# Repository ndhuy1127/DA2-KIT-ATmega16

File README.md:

# KIT phát triển ATmega16

Đồ án 2 – Học kỳ 20261 – Đại học Bách khoa Hà Nội

- **Mã lớp / mã đề tài:** 772645 / DA26111
- **Sinh viên thực hiện:** Nguyễn Đức Huy – 20233448
- **Giảng viên hướng dẫn:** ThS. Nguyễn Minh Đức

Đề tài thiết kế và lập trình một bo KIT dùng ATmega16. Trên bo có khối nguồn 5 V, thạch anh 8 MHz,
cổng nạp ISP cho USBasp, 8 LED đơn, 2 nút nhấn nối vào ngắt ngoài, biến trở để thử ADC, cổng UART,
chỗ cắm LCD1602 và bàn phím 4×4, cùng 4 header để đưa các cổng PORTA–PORTD ra ngoài.

## Tiến độ

| Tuần | Nội dung | Tài liệu | Trạng thái |
|------|----------|----------|------------|
| 1 | Tìm hiểu yêu cầu, datasheet, sơ đồ khối | [tuan-01](docs/tuan-01/yeu-cau-va-so-do-khoi.md) | Xong |
| 2 | Phân chân, chọn linh kiện, BOM | [pinmap](docs/tuan-02/pinmap.md), [BOM](docs/tuan-02/bom.md) | Xong |
| 3 | Vẽ schematic, ERC | [tuan-03](docs/tuan-03/schematic.md), [PDF](hardware/output/KIT-ATmega16-schematic.pdf) | Xong |
| 4 | Vẽ PCB, DRC, xuất Gerber | [tuan-04](docs/tuan-04/pcb.md), [Gerber](hardware/output/KIT-ATmega16-gerber.zip) | Xong |
| 5 | Mô phỏng GPIO, nút nhấn, ngắt ngoài, Timer | [tuan-05](docs/tuan-05/mo-phong.md), [firmware](firmware/labs) | Đang làm |
| 6 | Mô phỏng ADC, UART | | |
| 7 | Mô phỏng LCD1602, bàn phím 4×4 | | |
| 8 | Bài tổng hợp, hàn lắp bo | | |
| 9 | Chạy trên bo thật, đo kiểm | | |
| 10 | Báo cáo, slide, demo | | |

Lịch chi tiết xem ở [docs/ke-hoach/ke-hoach-dieu-chinh.md](docs/ke-hoach/ke-hoach-dieu-chinh.md).

## Thư mục

```
docs/          kế hoạch, phiếu báo cáo tuần, tài liệu từng tuần
hardware/      project KiCad, file xuất (PDF, Gerber, BOM, ảnh 3D) và script hỗ trợ
firmware/      mã nguồn các bài lab, board.h chứa phân chân dùng chung
simulation/    mạch mô phỏng Proteus
```

## Build firmware

Trên Windows cài avr-gcc bằng Scoop (`scoop install avr-gcc`), sau đó:

```powershell
cd firmware
powershell -ExecutionPolicy Bypass -File build.ps1                       # build hết, ra build/*.hex
powershell -ExecutionPolicy Bypass -File build.ps1 -Lab 04_timer -Flash  # build và nạp 1 bài qua USBasp
```

Với chip mới cần ghi fuse một lần để chạy thạch anh 8 MHz và tắt JTAG:

```bash
avrdude -c usbasp -p m16 -U lfuse:w:0xFF:m -U hfuse:w:0xD9:m
```

## Phần cứng

Mở `hardware/kicad/KIT-ATmega16.kicad_pro` bằng KiCad 10. Schematic chạy ERC không còn lỗi;
PCB chạy DRC không còn lỗi và khớp với schematic, chỉ còn vài cảnh báo chữ silkscreen bị chồng.

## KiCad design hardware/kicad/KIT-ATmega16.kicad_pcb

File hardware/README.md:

# Phần cứng

- `kicad/` – project KiCad 10 (`KIT-ATmega16.kicad_pro`), báo cáo ERC, DRC và netlist.
- `output/` – schematic PDF, file Gerber nén, BOM, ảnh 3D và bản in từng lớp.
- `scripts/` – các script Python hỗ trợ:
  - `design.py`: danh sách linh kiện, footprint và cách nối dây.
  - `gen_schematic.py`: tạo file schematic từ `design.py`.
  - `check_netlist.py`: so netlist KiCad với `design.py` để bắt chỗ nối sai.
  - `gen_pcb.py`: đặt linh kiện lên PCB, trao đổi với Freerouting để đi dây, đổ đồng GND.

## Chạy lại các bước

Cần KiCad 10 và Python 3. Riêng bước đi dây cần thêm Java 25 và `freerouting-2.5.0.jar`.

```bash
export KICAD_BIN="/c/Users/<user>/AppData/Local/Programs/KiCad/10.0/bin"
sh hardware/build_sch.sh      # tạo schematic, chạy ERC, xuất netlist, kiểm tra, xuất PDF

export JAVA="<java 25>/bin/java.exe"
export FREEROUTING="<đường dẫn>/freerouting-2.5.0.jar"
sh hardware/build_pcb.sh      # đặt linh kiện, đi dây, đổ đồng, chạy DRC, xuất Gerber, BOM, ảnh 3D
```

Lưu ý: `build_pcb.sh` đặt và đi dây lại từ đầu, nên sẽ ghi đè những gì đã chỉnh tay trên PCB. Khi đã sửa
layout trong KiCad thì chỉ chạy riêng các lệnh `kicad-cli pcb drc` và `export`.

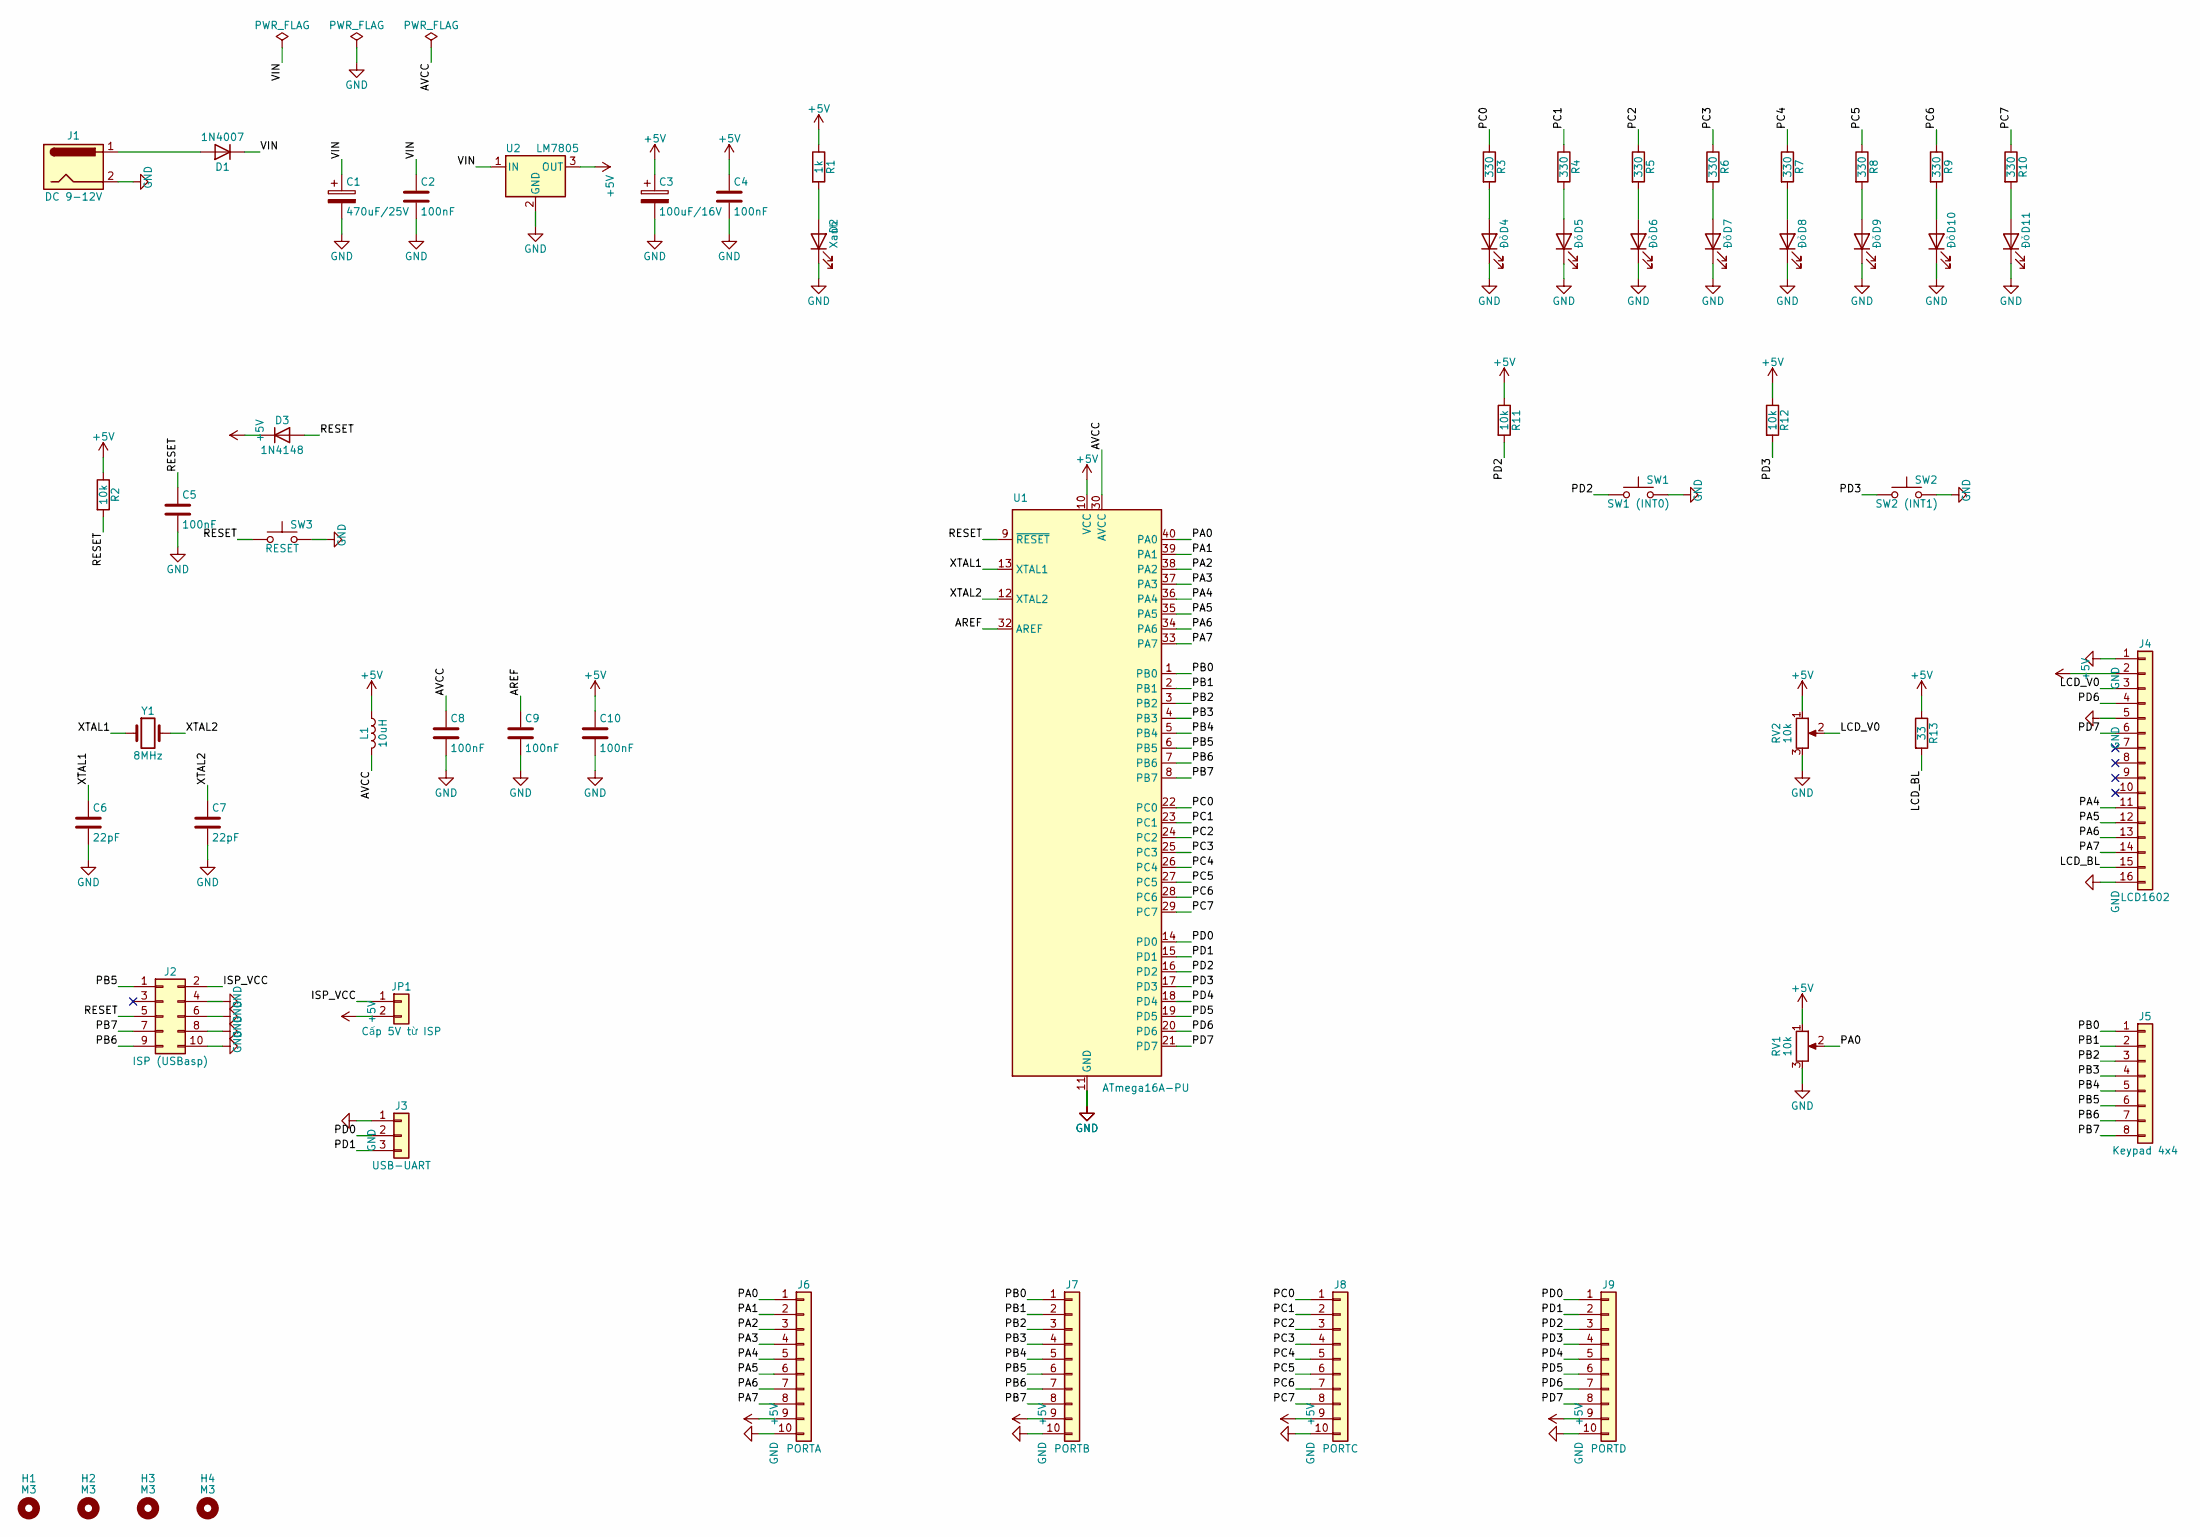
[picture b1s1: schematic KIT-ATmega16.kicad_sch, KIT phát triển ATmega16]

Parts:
C1: 470uF/25V; CP_Radial_D10.0mm_P5.00mm
C2, C4, C5, C8, C9, C10: 100nF; C_Disc_D5.0mm_W2.5mm_P5.00mm
C3: 100uF/16V; CP_Radial_D6.3mm_P2.50mm
C6, C7: 22pF; C_Disc_D5.0mm_W2.5mm_P5.00mm
D1: 1N4007; D_DO-41_SOD81_P10.16mm_Horizontal
D2: Xanh; LED_D3.0mm
D3: 1N4148; D_DO-35_SOD27_P7.62mm_Horizontal
D4, D5, D6, D7, D8, D9, D10, D11: Đỏ; LED_D3.0mm
H1, H2, H3, H4: M3; MountingHole_3.2mm_M3
J1: DC 9-12V; BarrelJack_Horizontal
J2: ISP (USBasp); IDC-Header_2x05_P2.54mm_Vertical
J3: USB-UART; PinHeader_1x03_P2.54mm_Vertical
J4: LCD1602; PinSocket_1x16_P2.54mm_Vertical
J5: Keypad 4x4; PinSocket_1x08_P2.54mm_Vertical
J6: PORTA; PinHeader_1x10_P2.54mm_Vertical
J7: PORTB; PinHeader_1x10_P2.54mm_Vertical
J8: PORTC; PinHeader_1x10_P2.54mm_Vertical
J9: PORTD; PinHeader_1x10_P2.54mm_Vertical
JP1: Cấp 5V từ ISP; PinHeader_1x02_P2.54mm_Vertical
L1: 10uH; L_Axial_L5.3mm_D2.2mm_P10.16mm_Horizontal_Vishay_IM-1
R1: 1k; R_Axial_DIN0207_L6.3mm_D2.5mm_P10.16mm_Horizontal
R2, R11, R12: 10k; R_Axial_DIN0207_L6.3mm_D2.5mm_P10.16mm_Horizontal
R3, R4, R5, R6, R7, R8, R9, R10: 330; R_Axial_DIN0207_L6.3mm_D2.5mm_P10.16mm_Horizontal
R13: 33; R_Axial_DIN0207_L6.3mm_D2.5mm_P10.16mm_Horizontal
RV1, RV2: 10k; Potentiometer_Bourns_3386P_Vertical
SW1: SW1 (INT0); SW_PUSH_6mm
SW2: SW2 (INT1); SW_PUSH_6mm
SW3: RESET; SW_PUSH_6mm
U1: ATmega16A-PU; DIP-40_W15.24mm_Socket
U2: LM7805; TO-220-3_Vertical
Y1: 8MHz; Crystal_HC49-U_Vertical

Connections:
+5V: C3.1, C4.1, C10.1, D3.1 (K), J4.2, J6.9, J7.9, J8.9, J9.9, JP1.2, L1.1, R1.1, R2.1, R11.1, R12.1, R13.1, RV1.1, RV2.1, U1.10 (VCC), U2.3 (OUT)
/AREF: C9.1, U1.32 (AREF)
/AVCC: C8.1, L1.2, U1.30 (AVCC)
/ISP_VCC: J2.2, JP1.1
/LCD_BL: J4.15, R13.2
/LCD_V0: J4.3, RV2.2
/PA0: J6.1, RV1.2, U1.40 (PA0)
/PA1: J6.2, U1.39 (PA1)
/PA2: J6.3, U1.38 (PA2)
/PA3: J6.4, U1.37 (PA3)
/PA4: J4.11, J6.5, U1.36 (PA4)
/PA5: J4.12, J6.6, U1.35 (PA5)
/PA6: J4.13, J6.7, U1.34 (PA6)
/PA7: J4.14, J6.8, U1.33 (PA7)
/PB0: J5.1, J7.1, U1.1 (PB0)
/PB1: J5.2, J7.2, U1.2 (PB1)
/PB2: J5.3, J7.3, U1.3 (PB2)
/PB3: J5.4, J7.4, U1.4 (PB3)
/PB4: J5.5, J7.5, U1.5 (PB4)
/PB5: J2.1, J5.6, J7.6, U1.6 (PB5)
/PB6: J2.9, J5.7, J7.7, U1.7 (PB6)
/PB7: J2.7, J5.8, J7.8, U1.8 (PB7)
/PC0: J8.1, R3.1, U1.22 (PC0)
/PC1: J8.2, R4.1, U1.23 (PC1)
/PC2: J8.3, R5.1, U1.24 (PC2)
/PC3: J8.4, R6.1, U1.25 (PC3)
/PC4: J8.5, R7.1, U1.26 (PC4)
/PC5: J8.6, R8.1, U1.27 (PC5)
/PC6: J8.7, R9.1, U1.28 (PC6)
/PC7: J8.8, R10.1, U1.29 (PC7)
/PD0: J3.2, J9.1, U1.14 (PD0)
/PD1: J3.3, J9.2, U1.15 (PD1)
/PD2: J9.3, R11.2, SW1.1, U1.16 (PD2)
/PD3: J9.4, R12.2, SW2.1, U1.17 (PD3)
/PD4: J9.5, U1.18 (PD4)
/PD5: J9.6, U1.19 (PD5)
/PD6: J4.4, J9.7, U1.20 (PD6)
/PD7: J4.6, J9.8, U1.21 (PD7)
/RESET: C5.1, D3.2 (A), J2.5, R2.2, SW3.1, U1.9 (~RESET)
/VIN: C1.1, C2.1, D1.1 (K), U2.1 (IN)
/XTAL1: C6.1, U1.13 (XTAL1), Y1.1
/XTAL2: C7.1, U1.12 (XTAL2), Y1.2
GND: C1.2, C2.2, C3.2, C4.2, C5.2, C6.2, C7.2, C8.2, C9.2, C10.2, D2.1 (K), D4.1 (K), D5.1 (K), D6.1 (K), D7.1 (K), D8.1 (K), D9.1 (K), D10.1 (K), D11.1 (K), J1.2, J2.4, J2.6, J2.8, J2.10, J3.1, J4.1, J4.5, J4.16, J6.10, J7.10, J8.10, J9.10, RV1.3, RV2.3, SW1.2, SW2.2, SW3.2, U1.11 (GND), U1.31 (GND), U2.2 (GND)
unnamed: D1.2 (A), J1.1
unnamed: D2.2 (A), R1.2
unnamed: D4.2 (A), R3.2
unnamed: D5.2 (A), R4.2
unnamed: D6.2 (A), R5.2
unnamed: D7.2 (A), R6.2
unnamed: D8.2 (A), R7.2
unnamed: D9.2 (A), R8.2
unnamed: D10.2 (A), R9.2
unnamed: D11.2 (A), R10.2

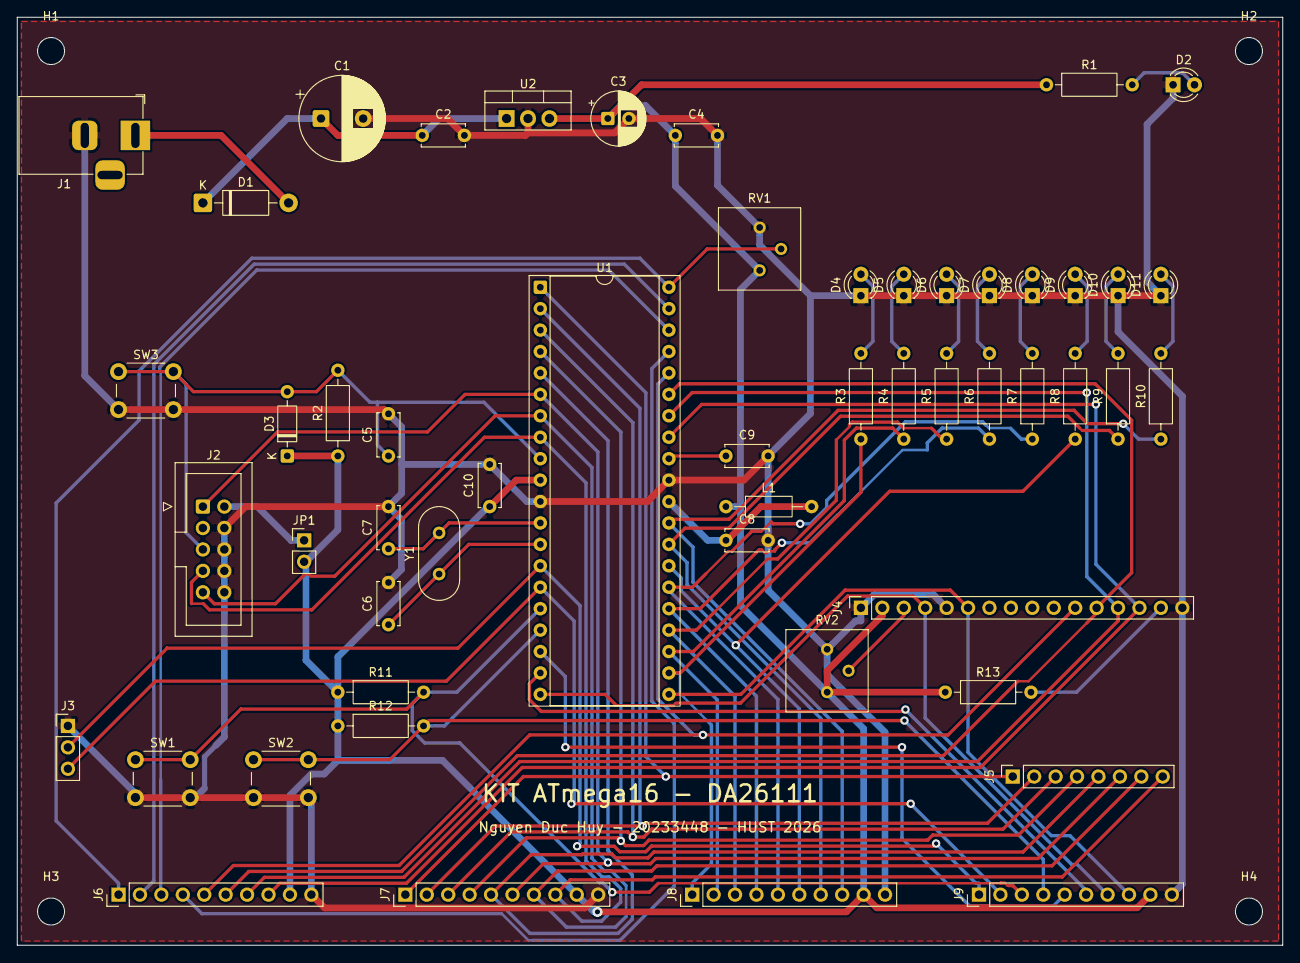
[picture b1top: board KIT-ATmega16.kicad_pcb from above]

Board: 2 copper layers, 150.0 x 110.0 mm, 57 parts (0 on the bottom side), 53 nets.

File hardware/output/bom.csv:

"Reference","Value","Footprint","QUANTITY"
"C1","470uF/25V","Capacitor_THT:CP_Radial_D10.0mm_P5.00mm","1"
"C2,C4,C5,C8-C10","100nF","Capacitor_THT:C_Disc_D5.0mm_W2.5mm_P5.00mm","6"
"C3","100uF/16V","Capacitor_THT:CP_Radial_D6.3mm_P2.50mm","1"
"C6,C7","22pF","Capacitor_THT:C_Disc_D5.0mm_W2.5mm_P5.00mm","2"
"D1","1N4007","Diode_THT:D_DO-41_SOD81_P10.16mm_Horizontal","1"
"D2","Xanh","LED_THT:LED_D3.0mm","1"
"D3","1N4148","Diode_THT:D_DO-35_SOD27_P7.62mm_Horizontal","1"
"D4-D11","Đỏ","LED_THT:LED_D3.0mm","8"
"J1","DC 9-12V","Connector_BarrelJack:BarrelJack_Horizontal","1"
"J2","ISP (USBasp)","Connector_IDC:IDC-Header_2x05_P2.54mm_Vertical","1"
"J3","USB-UART","Connector_PinHeader_2.54mm:PinHeader_1x03_P2.54mm_Vertical","1"
"J4","LCD1602","Connector_PinSocket_2.54mm:PinSocket_1x16_P2.54mm_Vertical","1"
"J5","Keypad 4x4","Connector_PinSocket_2.54mm:PinSocket_1x08_P2.54mm_Vertical","1"
"J6","PORTA","Connector_PinHeader_2.54mm:PinHeader_1x10_P2.54mm_Vertical","1"
"J7","PORTB","Connector_PinHeader_2.54mm:PinHeader_1x10_P2.54mm_Vertical","1"
"J8","PORTC","Connector_PinHeader_2.54mm:PinHeader_1x10_P2.54mm_Vertical","1"
"J9","PORTD","Connector_PinHeader_2.54mm:PinHeader_1x10_P2.54mm_Vertical","1"
"JP1","Cấp 5V từ ISP","Connector_PinHeader_2.54mm:PinHeader_1x02_P2.54mm_Vertical","1"
"L1","10uH","Inductor_THT:L_Axial_L5.3mm_D2.2mm_P10.16mm_Horizontal_Vishay_IM-1","1"
"R1","1k","Resistor_THT:R_Axial_DIN0207_L6.3mm_D2.5mm_P10.16mm_Horizontal","1"
"R2,R11,R12","10k","Resistor_THT:R_Axial_DIN0207_L6.3mm_D2.5mm_P10.16mm_Horizontal","3"
"R3-R10","330","Resistor_THT:R_Axial_DIN0207_L6.3mm_D2.5mm_P10.16mm_Horizontal","8"
"R13","33","Resistor_THT:R_Axial_DIN0207_L6.3mm_D2.5mm_P10.16mm_Horizontal","1"
"RV1,RV2","10k","Potentiometer_THT:Potentiometer_Bourns_3386P_Vertical","2"
"SW1","SW1 (INT0)","Button_Switch_THT:SW_PUSH_6mm","1"
"SW2","SW2 (INT1)","Button_Switch_THT:SW_PUSH_6mm","1"
"SW3","RESET","Button_Switch_THT:SW_PUSH_6mm","1"
"U1","ATmega16A-PU","Package_DIP:DIP-40_W15.24mm_Socket","1"
"U2","LM7805","Package_TO_SOT_THT:TO-220-3_Vertical","1"
"Y1","8MHz","Crystal:Crystal_HC49-U_Vertical","1"

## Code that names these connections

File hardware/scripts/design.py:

"""Dữ liệu thiết kế KIT ATmega16: linh kiện, footprint, vị trí trên schematic và net.

Đây là nguồn dữ liệu duy nhất của mạch nguyên lý. gen_schematic.py đọc file này
để sinh hardware/kicad/KIT-ATmega16.kicad_sch; check_netlist.py so sánh netlist
KiCad xuất ra với bảng net ở đây.

Quy ước net:
  "+5V", "GND"      -> vẽ bằng power symbol
  "~TEN"            -> nối bằng dây trực tiếp giữa các chân (các chân phải thẳng hàng)
  None              -> chân bỏ trống, đặt cờ no-connect
  tên khác          -> nối bằng nhãn (label) cùng tên
Tọa độ schematic tính bằng mm, gốc ở góc trên-trái, y hướng xuống.
"""

FP = {
    'R': 'Resistor_THT:R_Axial_DIN0207_L6.3mm_D2.5mm_P10.16mm_Horizontal',
    'C': 'Capacitor_THT:C_Disc_D5.0mm_W2.5mm_P5.00mm',
    'CP10': 'Capacitor_THT:CP_Radial_D10.0mm_P5.00mm',
    'CP6': 'Capacitor_THT:CP_Radial_D6.3mm_P2.50mm',
    'LED': 'LED_THT:LED_D3.0mm',
    'POT': 'Potentiometer_THT:Potentiometer_Bourns_3386P_Vertical',
    'SW': 'Button_Switch_THT:SW_PUSH_6mm',
    'H10': 'Connector_PinHeader_2.54mm:PinHeader_1x10_P2.54mm_Vertical',
}

COMPONENTS = []


def add(ref, lib, value, fp, x, y, pins, rot=0, desc='', in_bom=True):
    COMPONENTS.append(dict(ref=ref, lib=lib, value=value, fp=fp, x=x, y=y,
                           rot=rot, pins=pins, desc=desc, in_bom=in_bom))


# ---------------------------------------------------------------- Khối nguồn
add('J1', 'Connector:Barrel_Jack', 'DC 9-12V', 'Connector_BarrelJack:BarrelJack_Horizontal',
    30.48, 45.72, {'1': '~VJACK', '2': 'GND'}, desc='Jack nguồn DC 5.5/2.1 mm')
add('D1', 'Diode:1N4007', '1N4007', 'Diode_THT:D_DO-41_SOD81_P10.16mm_Horizontal',
    55.88, 43.18, {'1': 'VIN', '2': '~VJACK'}, rot=180, desc='Chống cắm ngược cực')
add('C1', 'Device:C_Polarized', '470uF/25V', FP['CP10'], 76.2, 50.8, {'1': 'VIN', '2': 'GND'})
add('C2', 'Device:C', '100nF', FP['C'], 88.9, 50.8, {'1': 'VIN', '2': 'GND'})
add('U2', 'Regulator_Linear:L7805', 'LM7805', 'Package_TO_SOT_THT:TO-220-3_Vertical',
    109.22, 45.72, {'1': 'VIN', '2': 'GND', '3': '+5V'}, desc='Ổn áp 5 V')
add('C3', 'Device:C_Polarized', '100uF/16V', FP['CP6'], 129.54, 50.8, {'1': '+5V', '2': 'GND'})
add('C4', 'Device:C', '100nF', FP['C'], 142.24, 50.8, {'1': '+5V', '2': 'GND'})
add('R1', 'Device:R', '1k', FP['R'], 157.48, 45.72, {'1': '+5V', '2': '~LED_PWR'})
add('D2', 'Device:LED', 'Xanh', FP['LED'], 157.48, 58.42, {'2': '~LED_PWR', '1': 'GND'}, rot=90)
add('#FLG01', 'power:PWR_FLAG', 'PWR_FLAG', '', 66.04, 25.4, {'1': 'VIN'})
add('#FLG02', 'power:PWR_FLAG', 'PWR_FLAG', '', 78.74, 25.4, {'1': 'GND'})
add('#FLG03', 'power:PWR_FLAG', 'PWR_FLAG', '', 91.44, 25.4, {'1': 'AVCC'})

# ------------------------------------------------------ Reset, clock, AVCC
add('R2', 'Device:R', '10k', FP['R'], 35.56, 101.6, {'1': '+5V', '2': 'RESET'})
add('C5', 'Device:C', '100nF', FP['C'], 48.26, 104.14, {'1': 'RESET', '2': 'GND'})
add('SW3', 'Switch:SW_Push', 'RESET', FP['SW'], 66.04, 109.22, {'1': 'RESET', '2': 'GND'})
add('D3', 'Diode:1N4148', '1N4148', 'Diode_THT:D_DO-35_SOD27_P7.62mm_Horizontal',
    66.04, 91.44, {'1': '+5V', '2': 'RESET'}, desc='Kẹp xung ESD trên RESET (AN2519)')
add('Y1', 'Device:Crystal', '8MHz', 'Crystal:Crystal_HC49-U_Vertical',
    43.18, 142.24, {'1': 'XTAL1', '2': 'XTAL2'})
add('C6', 'Device:C', '22pF', FP['C'], 33.02, 157.48, {'1': 'XTAL1', '2': 'GND'})
add('C7', 'Device:C', '22pF', FP['C'], 53.34, 157.48, {'1': 'XTAL2', '2': 'GND'})
add('L1', 'Device:L', '10uH', 'Inductor_THT:L_Axial_L5.3mm_D2.2mm_P10.16mm_Horizontal_Vishay_IM-1',
    81.28, 142.24, {'1': '+5V', '2': 'AVCC'}, desc='Lọc nguồn analog (AN2519)')
add('C8', 'Device:C', '100nF', FP['C'], 93.98, 142.24, {'1': 'AVCC', '2': 'GND'})
add('C9', 'Device:C', '100nF', FP['C'], 106.68, 142.24, {'1': 'AREF', '2': 'GND'})
add('C10', 'Device:C', '100nF', FP['C'], 119.38, 142.24, {'1': '+5V', '2': 'GND'}, desc='Tụ thoát VCC sát chân 10')

# ------------------------------------------------------------------- MCU
MCU_PINS = {'9': 'RESET', '10': '+5V', '11': 'GND', '31': 'GND', '12': 'XTAL2', '13': 'XTAL1',
            '30': ('AVCC', 7.62), '32': 'AREF'}
for i in range(8):
    MCU_PINS[str(40 - i)] = f'PA{i}'
    MCU_PINS[str(1 + i)] = f'PB{i}'
    MCU_PINS[str(22 + i)] = f'PC{i}'
    MCU_PINS[str(14 + i)] = f'PD{i}'
add('U1', 'MCU_Microchip_ATmega:ATmega16A-P', 'ATmega16A-PU', 'Package_DIP:DIP-40_W15.24mm_Socket',
    203.2, 152.4, MCU_PINS)

# ------------------------------------------------------------ ISP, UART
add('J2', 'Connector_Generic:Conn_02x05_Odd_Even', 'ISP (USBasp)', 'Connector_IDC:IDC-Header_2x05_P2.54mm_Vertical',
    45.72, 190.5, {'1': 'PB5', '2': 'ISP_VCC', '3': None, '4': 'GND', '5': 'RESET',
                   '6': 'GND', '7': 'PB7', '8': 'GND', '9': 'PB6', '10': 'GND'})
add('JP1', 'Connector_Generic:Conn_01x02', 'Cấp 5V từ ISP', 'Connector_PinHeader_2.54mm:PinHeader_1x02_P2.54mm_Vertical',
    86.36, 187.96, {'1': 'ISP_VCC', '2': '+5V'})
add('J3', 'Connector_Generic:Conn_01x03', 'USB-UART', 'Connector_PinHeader_2.54mm:PinHeader_1x03_P2.54mm_Vertical',
    86.36, 210.82, {'1': 'GND', '2': 'PD0', '3': 'PD1'}, desc='Pin2 RXD <- TX module; Pin3 TXD -> RX module')

# ------------------------------------------------------ LED đơn PORTC
for i in range(8):
    x = 271.78 + 12.7 * i
    add(f'R{3 + i}', 'Device:R', '330', FP['R'], x, 45.72, {'1': f'PC{i}', '2': f'~LED{i}'})
    add(f'D{4 + i}', 'Device:LED', 'Đỏ', FP['LED'], x, 58.42, {'2': f'~LED{i}', '1': 'GND'}, rot=90)

# ---------------------------------------------------- Nút nhấn INT0/INT1
add('R11', 'Device:R', '10k', FP['R'], 274.32, 88.9, {'1': '+5V', '2': 'PD2'})
add('SW1', 'Switch:SW_Push', 'SW1 (INT0)', FP['SW'], 297.18, 101.6, {'1': 'PD2', '2': 'GND'})
add('R12', 'Device:R', '10k', FP['R'], 320.04, 88.9, {'1': '+5V', '2': 'PD3'})
add('SW2', 'Switch:SW_Push', 'SW2 (INT1)', FP['SW'], 342.9, 101.6, {'1': 'PD3', '2': 'GND'})

# ------------------------------------------------------------- LCD1602
LCD = {'1': 'GND', '2': ('+5V', 7.62), '3': 'LCD_V0', '4': 'PD6', '5': 'GND', '6': 'PD7',
       '7': None, '8': None, '9': None, '10': None,
       '11': 'PA4', '12': 'PA5', '13': 'PA6', '14': 'PA7', '15': 'LCD_BL', '16': 'GND'}
add('J4', 'Connector_Generic:Conn_01x16', 'LCD1602', 'Connector_PinSocket_2.54mm:PinSocket_1x16_P2.54mm_Vertical',
    383.54, 147.32, LCD, desc='Chế độ 4 bit, RW nối GND')
add('RV2', 'Device:R_Potentiometer', '10k', FP['POT'], 325.12, 142.24,
    {'1': '+5V', '2': 'LCD_V0', '3': 'GND'}, desc='Chỉnh độ tương phản LCD')
add('R13', 'Device:R', '33', FP['R'], 345.44, 142.24, {'1': '+5V', '2': 'LCD_BL'}, desc='Hạn dòng đèn nền')

# -------------------------------------------------- Ma trận phím, ADC
KEY = {str(i + 1): f'PB{i}' for i in range(8)}
add('J5', 'Connector_Generic:Conn_01x08', 'Keypad 4x4', 'Connector_PinSocket_2.54mm:PinSocket_1x08_P2.54mm_Vertical',
    383.54, 200.66, KEY, desc='Pin1..4 = hàng R1..R4, pin5..8 = cột C1..C4')
add('RV1', 'Device:R_Potentiometer', '10k', FP['POT'], 325.12, 195.58,
    {'1': '+5V', '2': 'PA0', '3': 'GND'}, desc='Biến trở thử ADC0')

# ------------------------------------------------- Header mở rộng cổng
for k, port in enumerate('ABCD'):
    pins = {str(i + 1): f'P{port}{i}' for i in range(8)}
    pins.update({'9': '+5V', '10': 'GND'})
    add(f'J{6 + k}', 'Connector_Generic:Conn_01x10', f'PORT{port}', FP['H10'],
        154.94 + 45.72 * k, 248.92, pins)

# ------------------------------------------------------------ Lỗ bắt vít
for k in range(4):
    add(f'H{k + 1}', 'Mechanical:MountingHole', 'M3', 'MountingHole:MountingHole_3.2mm_M3',
        22.86 + 10.16 * k, 274.32, {}, in_bom=False)

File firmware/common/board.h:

/*
 * board.h - Bảng phân chân (pin map) KIT ATmega16
 *
 * Nguồn gốc: docs/tuan-02/pinmap.md. Mọi thay đổi phân chân phải sửa đồng thời
 * ở file này, ở pinmap.md và ở schematic (hardware/kicad).
 *
 * Clock: thạch anh ngoài 8 MHz (fuse CKSEL = 1111, SUT = 11).
 * JTAG phải tắt (fuse JTAGEN = 1) để dùng PC2..PC5 làm GPIO cho LED.
 */
#ifndef BOARD_H
#define BOARD_H

#ifndef F_CPU
#define F_CPU 8000000UL
#endif

#include <avr/io.h>

/* ---- LED đơn: 8 LED nối PORTC, tích cực mức cao (qua R 330 Ω xuống GND) ---- */
#define LED_DDR        DDRC
#define LED_PORT       PORTC

/* ---- Nút nhấn: kéo lên 10 kΩ, nhấn = mức 0 ---- */
#define BTN_DDR        DDRD
#define BTN_PORT       PORTD
#define BTN_PIN        PIND
#define BTN1_BIT       PD2     /* SW1 -> INT0 */
#define BTN2_BIT       PD3     /* SW2 -> INT1 */

/* ---- Timer/Counter: chân so sánh ra để quan sát bằng oscilloscope ---- */
#define OC1A_DDR       DDRD
#define OC1A_BIT       PD5     /* OC1A */
#define OC0_DDR        DDRB
#define OC0_BIT        PB3     /* OC0 (dùng chung hàng phím ROW3, chỉ dùng khi không gắn phím) */

/* ---- ADC: biến trở VR1 nối ADC0 (PA0), tham chiếu AVCC ---- */
#define ADC_POT_CH     0

/* ---- UART: PD0 = RXD, PD1 = TXD -> module USB-UART (CP2102/CH340) ---- */
#define UART_BAUD      9600UL

/* ---- LCD1602 chế độ 4 bit: D4..D7 = PA4..PA7, RS = PD6, EN = PD7, RW nối GND ---- */
#define LCD_DATA_DDR   DDRA
#define LCD_DATA_PORT  PORTA
#define LCD_D4_BIT     PA4
#define LCD_CTRL_DDR   DDRD
#define LCD_CTRL_PORT  PORTD
#define LCD_RS_BIT     PD6
#define LCD_EN_BIT     PD7

/* ---- Ma trận phím 4x4: hàng PB0..PB3 (ra), cột PB4..PB7 (vào, kéo lên nội) ---- */
#define KEY_DDR        DDRB
#define KEY_PORT       PORTB
#define KEY_PIN        PINB
#define KEY_ROW_MASK   0x0F
#define KEY_COL_MASK   0xF0

#endif /* BOARD_H */

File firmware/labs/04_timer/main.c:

/*
 * Bài 04 - Timer/Counter
 *
 *   Timer1, chế độ CTC (TOP = OCR1A), đảo chân OC1A (PD5) bằng phần cứng:
 *     f_OC1A = F_CPU / (2 * N * (1 + OCR1A)) = 8 MHz / (2 * 8 * 500) = 1 kHz
 *     -> đo bằng oscilloscope / frequency counter trên mô phỏng để kiểm chứng.
 *   Timer0, chế độ CTC, ngắt mỗi 1 ms:
 *     OCR0 = F_CPU / (64 * 1000) - 1 = 124
 *     -> tạo nhịp hệ thống millis(); PC0 nháy 1 Hz, PC1 nháy 5 Hz,
 *        số giây (mod 64) hiển thị nhị phân trên PC2..PC7.
 */
#include "board.h"
#include <avr/interrupt.h>
#include <stdint.h>

static volatile uint32_t ms_ticks;

ISR(TIMER0_COMP_vect)
{
    ms_ticks++;
}

static uint32_t millis(void)
{
    uint32_t t;
    cli();
    t = ms_ticks;
    sei();
    return t;
}

static void timer0_1ms_init(void)
{
    TCCR0 = (1 << WGM01) | (1 << CS01) | (1 << CS00);   /* CTC, N = 64 */
    OCR0 = (uint8_t)(F_CPU / 64 / 1000 - 1);
    TIMSK |= (1 << OCIE0);
}

static void timer1_1khz_init(void)
{
    OC1A_DDR |= (1 << OC1A_BIT);
    TCCR1A = (1 << COM1A0);                     /* đảo OC1A mỗi lần so khớp */
    TCCR1B = (1 << WGM12) | (1 << CS11);        /* CTC (TOP = OCR1A), N = 8 */
    OCR1A = (uint16_t)(F_CPU / (2UL * 8 * 1000) - 1);
}

int main(void)
{
    LED_DDR = 0xFF;
    LED_PORT = 0;

    timer0_1ms_init();
    timer1_1khz_init();
    sei();

    uint32_t t_slow = 0, t_fast = 0;
    uint8_t seconds = 0, leds = 0;

    for (;;) {
        uint32_t now = millis();

        if (now - t_fast >= 100) {              /* 5 Hz: đảo mỗi 100 ms */
            t_fast += 100;
            leds ^= 0x02;
        }
        if (now - t_slow >= 500) {              /* 1 Hz: đảo mỗi 500 ms */
            t_slow += 500;
            leds ^= 0x01;
            if (!(leds & 0x01))
                seconds = (seconds + 1) & 0x3F;
        }
        LED_PORT = (uint8_t)((seconds << 2) | (leds & 0x03));
    }
}
